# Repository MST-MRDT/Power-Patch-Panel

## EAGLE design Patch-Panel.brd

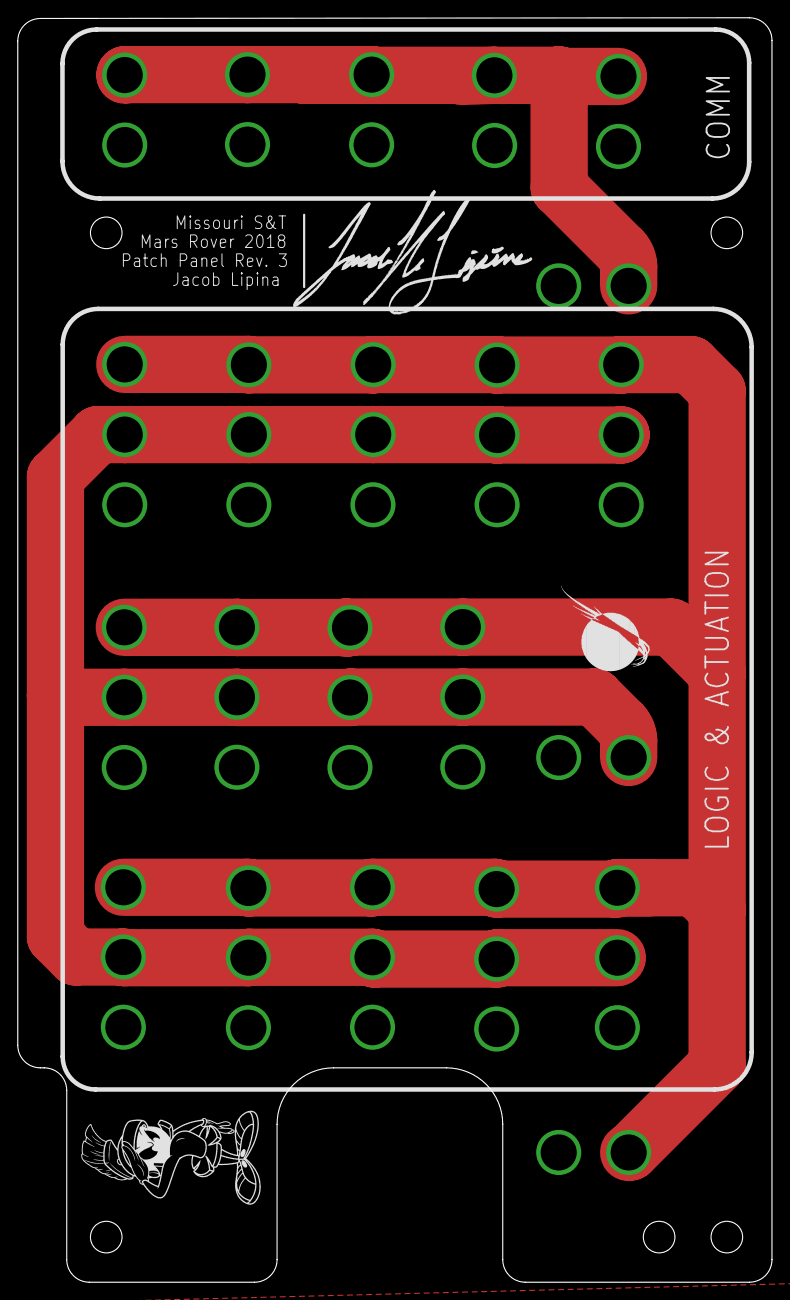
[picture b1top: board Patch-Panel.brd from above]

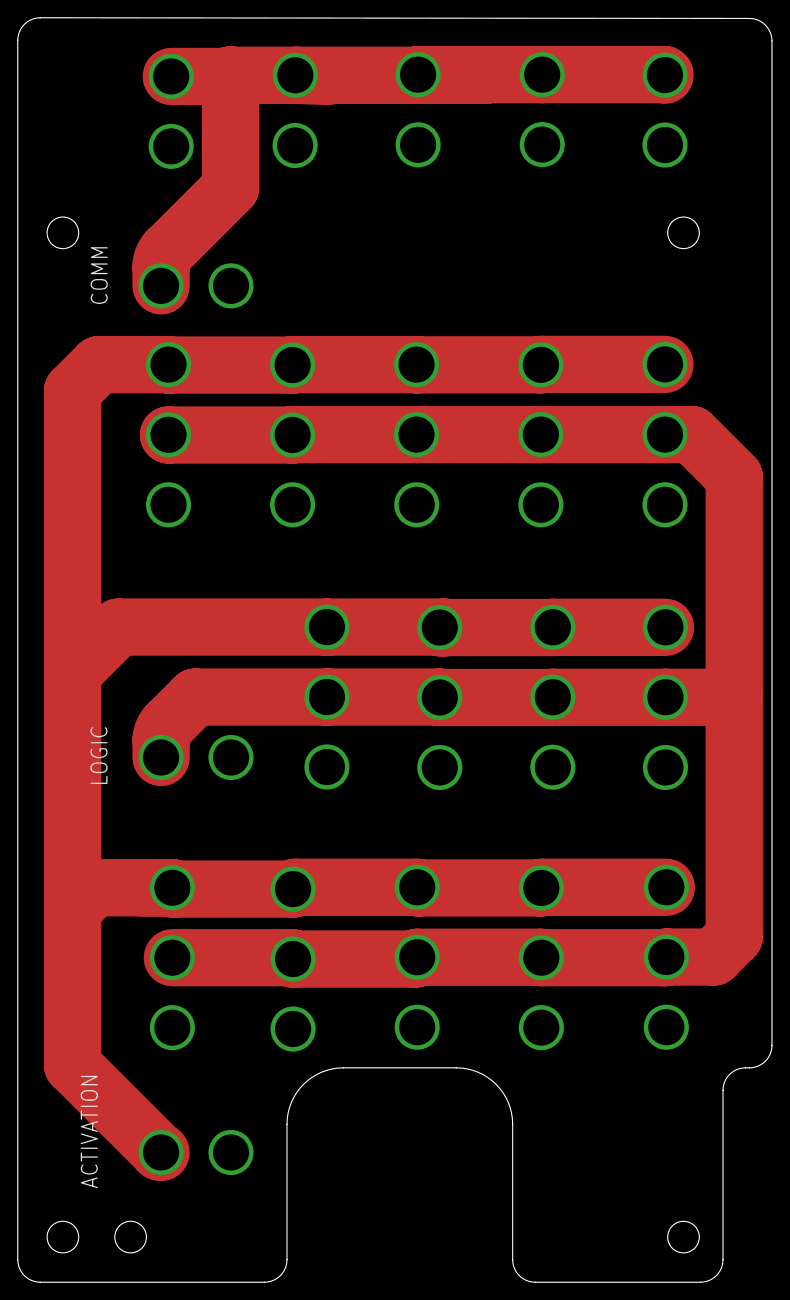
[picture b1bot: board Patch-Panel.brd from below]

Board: 2 copper layers, 84.9 x 142.3 mm, 66 parts (6 on the bottom side), 4 nets.

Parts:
H3, H4, H5, H6, H7: MOUNTING_HOLE#6; #6_SCREW
J1, J2, J3, J4, J5, J6, J7, J8, J9, J10, J11, J12, J13, J14, J15, J16, J17, J18, J19, J20, J21, J22, J23, J24, J25, J26, J27, J28, J29, J30, J31, J32, J33, J34, J35, J36, J37, J38, J39, J40, J41, J42, J43, J44, J45, J46, J47, J48, J49, J50, J51, J52, J53, J54, J55, J56, J57, J58: APPPP45_PCB_VERT; APP45_PCB_VERT
LOGO1: MRDT_LOGO
U$1: JACOB_SIG
U$2: MARVIN-THE-MARTIAN; MARVIN

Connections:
ACT-12V: J1.P$1, J9.P$1, J12.P$1, J15.P$1, J18.P$1, J21.P$1, J24.P$1, J27.P$1, J38.P$1, J41.P$1, J46.P$1, J49.P$1, J52.P$1, J55.P$1, J58.P$1
COM-12V: J5.P$1, J28.P$1, J30.P$1, J32.P$1, J34.P$1, J44.P$1
GND: J2.P$1, J4.P$1, J6.P$1, J7.P$1, J10.P$1, J13.P$1, J16.P$1, J19.P$1, J22.P$1, J25.P$1, J29.P$1, J31.P$1, J33.P$1, J35.P$1, J36.P$1, J39.P$1, J42.P$1, J45.P$1, J47.P$1, J50.P$1, J53.P$1, J56.P$1
LOG-12V: J3.P$1, J8.P$1, J11.P$1, J14.P$1, J17.P$1, J20.P$1, J23.P$1, J26.P$1, J37.P$1, J40.P$1, J43.P$1, J48.P$1, J51.P$1, J54.P$1, J57.P$1

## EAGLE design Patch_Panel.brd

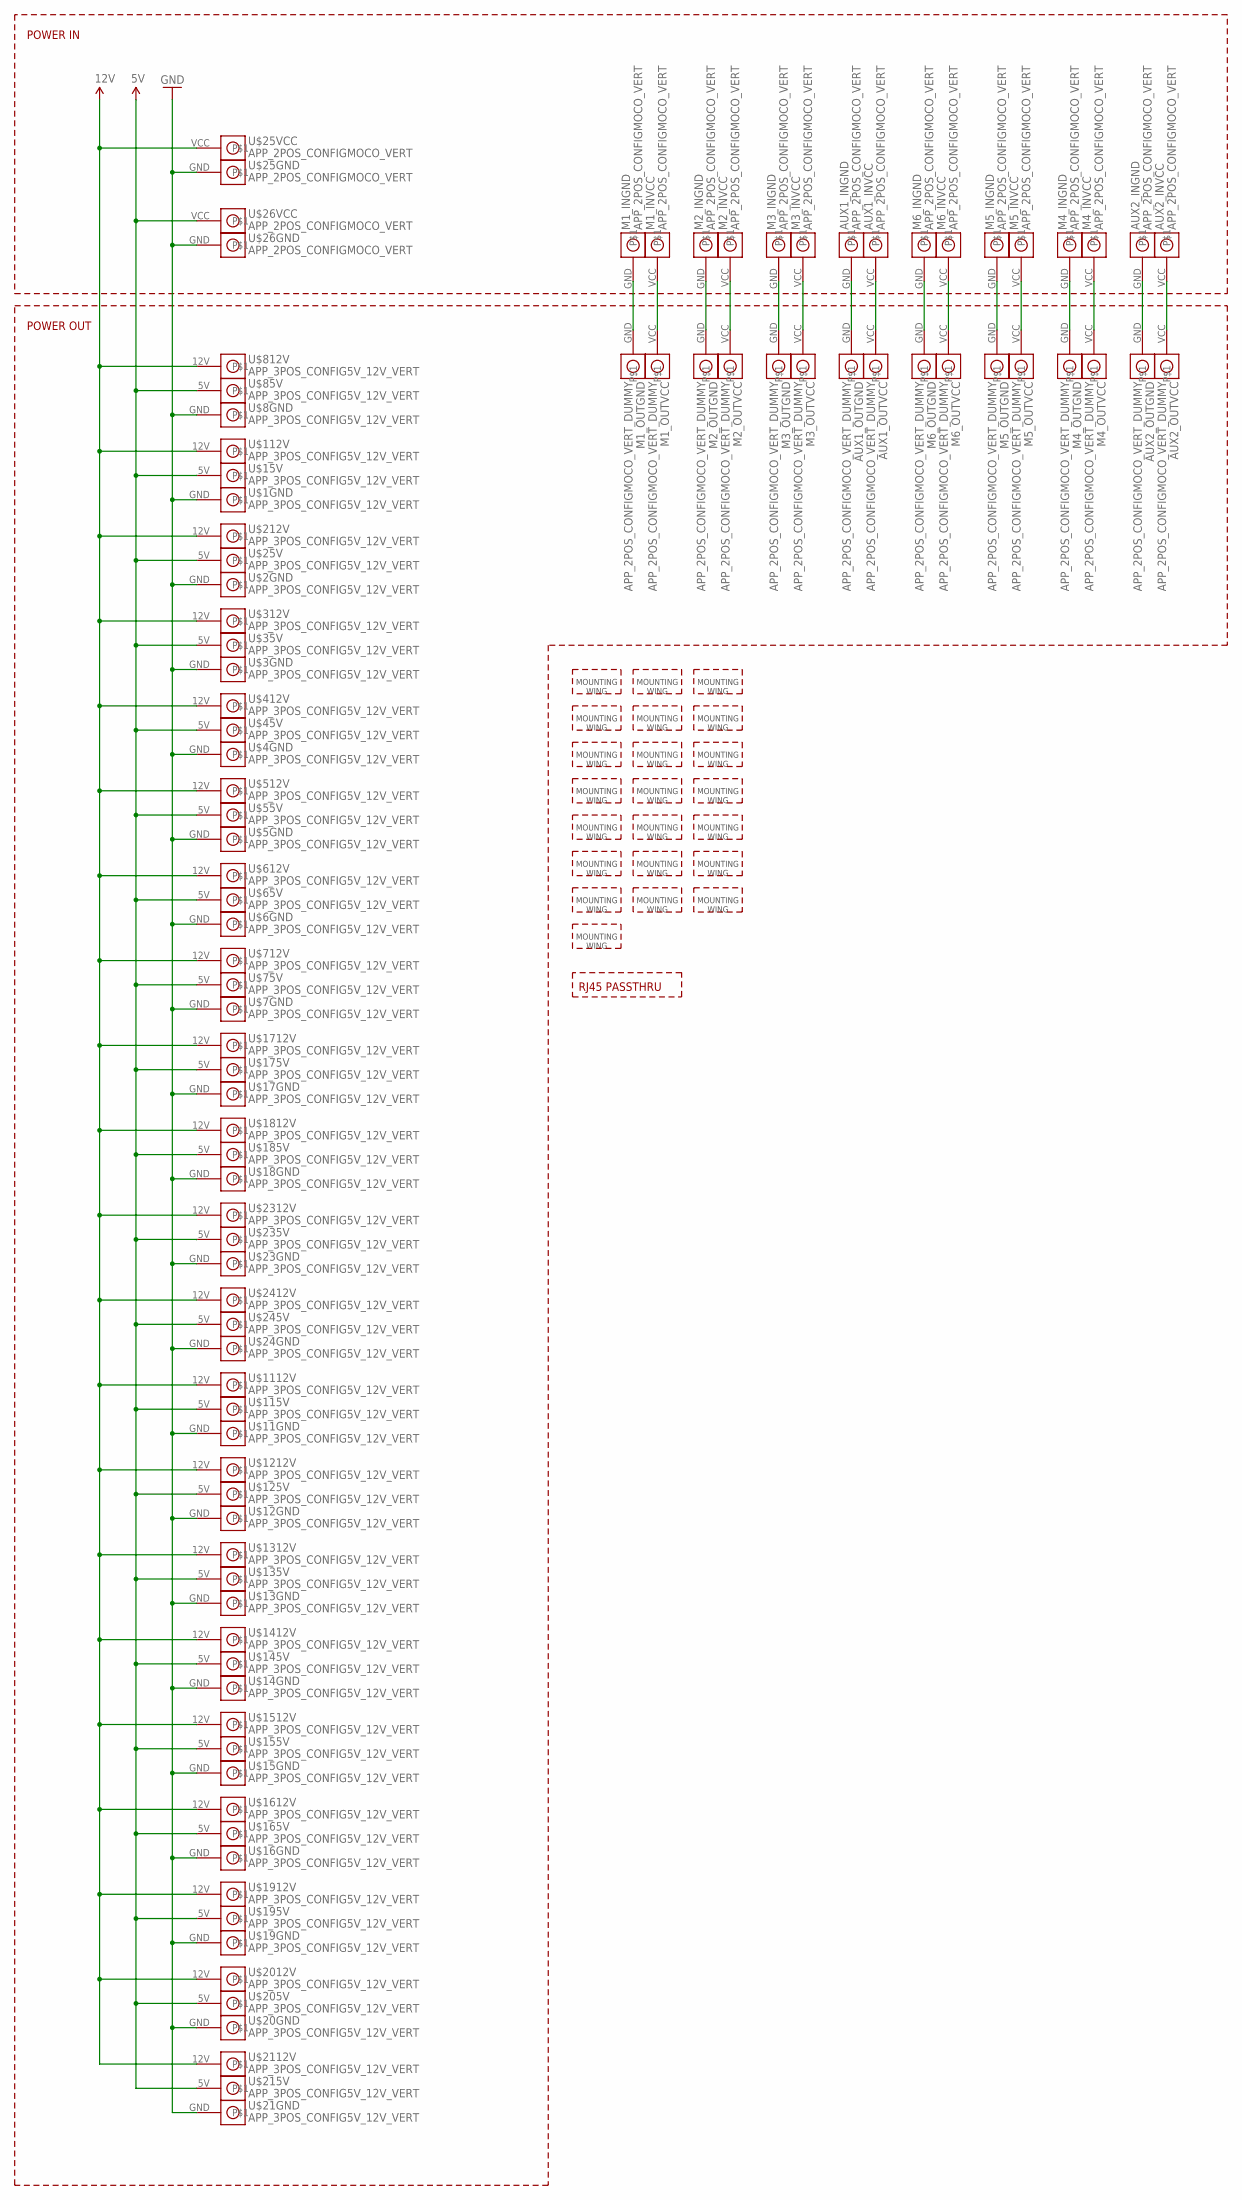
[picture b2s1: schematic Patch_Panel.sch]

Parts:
AUX1_IN, AUX2_IN: APP_2POS_CONFIGMOCO_VERT; APP45_MOCO_VERT_CONFIG
AUX1_OUT, AUX2_OUT: APP_2POS_CONFIGMOCO_VERT_DUMMY; APP45_MOCO_VERT_CONFIG_DUMMY
M1_IN, M2_IN, M3_IN, M4_IN, M5_IN, M6_IN: APP_2POS_CONFIGMOCO_VERT; APP45_MOCO_VERT_CONFIG
M1_OUT, M2_OUT, M3_OUT, M4_OUT, M5_OUT, M6_OUT: APP_2POS_CONFIGMOCO_VERT_DUMMY; APP45_MOCO_VERT_CONFIG_DUMMY
U$1, U$2, U$3, U$4, U$5, U$6, U$7, U$8, U$11, U$12, U$13, U$14, U$15, U$16, U$17, U$18, U$19, U$20, U$21, U$23, U$24: APP_3POS_CONFIG5V_12V_VERT; APP45_5V_12V_VERT_CONFIG
U$9, U$10, U$22, U$27, U$28, U$29, U$30, U$31, U$32, U$33, U$34, U$35, U$36, U$37, U$38, U$39, U$40, U$41, U$42, U$43, U$44, U$45: APP_MOUTING_WINGVERT; APP45_MOUNTING_WING_VERT
U$25, U$26: APP_2POS_CONFIGMOCO_VERT; APP45_MOCO_VERT_CONFIG
U$46: RJ45_PASSTHRUMRDT_MALE_RJ45_STANDOFF; MRDT_MALE_RJ45_STANDOFF

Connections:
5V: U$1.5V, U$2.5V, U$3.5V, U$4.5V, U$5.5V, U$6.5V, U$7.5V, U$8.5V, U$11.5V, U$12.5V, U$13.5V, U$14.5V, U$15.5V, U$16.5V, U$17.5V, U$18.5V, U$19.5V, U$20.5V, U$21.5V, U$23.5V, U$24.5V, U$26.VCC
12V: U$1.12V, U$2.12V, U$3.12V, U$4.12V, U$5.12V, U$6.12V, U$7.12V, U$8.12V, U$11.12V, U$12.12V, U$13.12V, U$14.12V, U$15.12V, U$16.12V, U$17.12V, U$18.12V, U$19.12V, U$20.12V, U$21.12V, U$23.12V, U$24.12V, U$25.VCC
AUX1_VCC: AUX1_IN.VCC, AUX1_OUT.VCC
AUX2_VCC: AUX2_IN.VCC, AUX2_OUT.VCC
GND: AUX1_IN.GND, AUX1_OUT.GND, AUX2_IN.GND, AUX2_OUT.GND, M1_IN.GND, M1_OUT.GND, M2_IN.GND, M2_OUT.GND, M3_IN.GND, M3_OUT.GND, M4_IN.GND, M4_OUT.GND, M5_IN.GND, M5_OUT.GND, M6_IN.GND, M6_OUT.GND, U$1.GND, U$2.GND, U$3.GND, U$4.GND, U$5.GND, U$6.GND, U$7.GND, U$8.GND, U$11.GND, U$12.GND, U$13.GND, U$14.GND, U$15.GND, U$16.GND, U$17.GND, U$18.GND, U$19.GND, U$20.GND, U$21.GND, U$23.GND, U$24.GND, U$25.GND, U$26.GND
M1_VCC: M1_IN.VCC, M1_OUT.VCC
M2_VCC: M2_IN.VCC, M2_OUT.VCC
M3_VCC: M3_IN.VCC, M3_OUT.VCC
M4_VCC: M4_IN.VCC, M4_OUT.VCC
M5_VCC: M5_IN.VCC, M5_OUT.VCC
M6_VCC: M6_IN.VCC, M6_OUT.VCC

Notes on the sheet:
POWER IN
POWER OUT

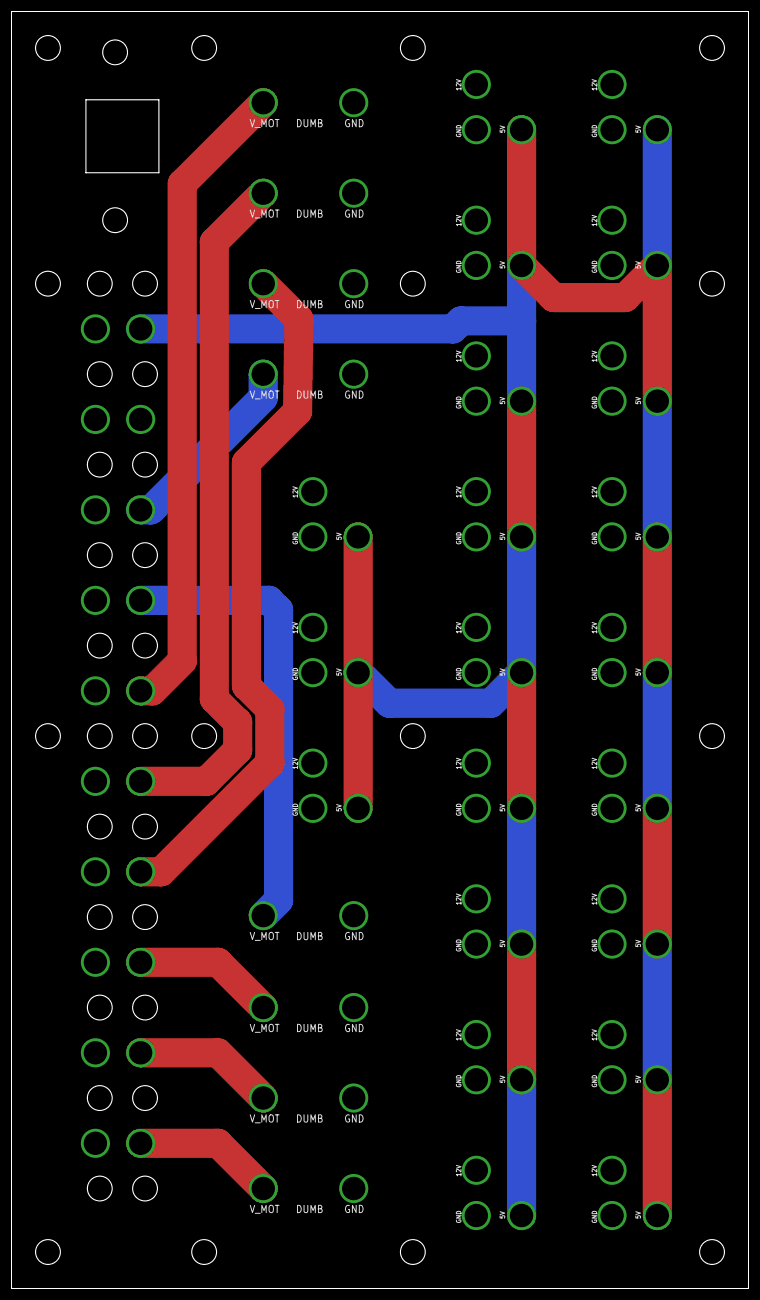
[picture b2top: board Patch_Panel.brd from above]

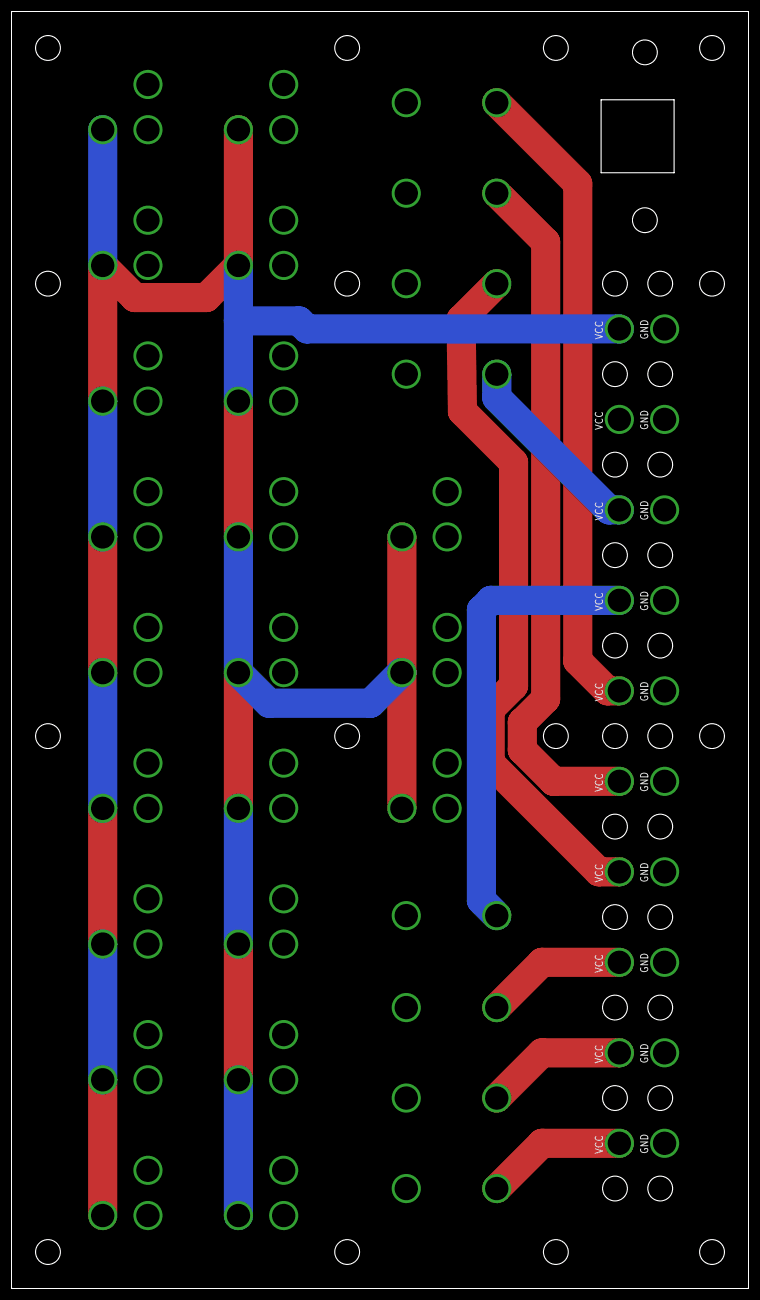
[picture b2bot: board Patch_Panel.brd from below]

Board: 2 copper layers, 128.3 x 222.2 mm, 62 parts (32 on the bottom side), 11 nets.

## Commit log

2015-11-01 Create patch panel V1
2015-11-01 Added BOM
2015-11-17 Remove unnecessary backup files
2015-11-17 Update gitignore
2015-12-02 Removed 2-pin Connectors and RJ45 Pass-Through
2016-01-13 added moco power patch-thru, rearr 3-pin, gen dx
2016-01-13 Revert "added moco power patch-thru, rearr 3-pin, gen dx"
    This reverts commit e393c53abb352ea2a1f007c95e73af8e49a976a5.
2016-01-13 un-deleted brd file and re-added dxf
2016-01-13 imported new mlx connectors
2016-01-15 totally re-made patch panel, gen dxf
2016-01-15 added missing route
2016-01-16 Added ethernet hole
2016-01-19 added cutout, rerouted w/ vert app connectors for power in
2016-01-19 added rj45 standoff - needs placed
2016-01-21 github sucks. i changed some stuff
2016-01-22 FINAL PATCH PANEL REV 1
2016-11-06 2017 Patch Panel
    This patch panel for 2017 has 4 connections for the Logic bus, 6
    connections for the Logic & Actuation bus, 4 connections for the
    Actuation bus, and 2 connections for an extra bus.
2016-11-08 Last edits before fabrication
    tidied a couple traces and labels, and added a martian.
2017-11-08 2018 Patch Panel Rev1
    The 12V buses are being passed to patch panel. In order from bottom of power board to top, Actuation 15A, Logic 5A, Communication 5A. There is no extra bus this year. Add one more Logic/Act connection
2017-11-09 Font changed to vector
2018-03-15 Patch Panel Rev 2
    Eliminates all exclusive logic buses and added seven more actuation/logic combo buses. Added one more comm bus
2018-03-25 Rev.3 to Change Mounting Hole Locations
    Mounting holes on Rev.2 are incorrect because power board's size changed slightly and we only realized the holes didnt match up after we ordered Rev.2
2018-03-26 Adjusted bottom anderson positions
2018-03-26 Added gitignore and fixed silkscreen
2018-12-07 Created project and completed schematic
2018-12-13 Added Packages to Library
2018-12-13 Symbols named and packages assigned
2018-12-13 Outline and Hole Placement Complete
2018-12-13 Placed Double Andersons
2018-12-14 Placed Connectors & Routed Traces
2018-12-14 Added Silkscreen
2018-12-14 Created BOM
2018-12-31 Created Gerbs
2019-01-17 update rev 2 library
2019-10-08 layout
2019-10-10 board
2019-10-10 finished PCBdesign
2019-10-10 ready for PDR
2019-10-31 ready for board review
2019-11-18 add input label
2019-11-21 final change
2019-11-21 before review
2019-11-26 fixed board review issue
2019-12-06 matching
2019-12-11 change molex
2019-12-11 add LED to anderson
2019-12-11 BoardReview
2019-12-11 add gerbs
2019-12-14 bom.scv
2019-12-15 fix bom file
2020-01-21 Created Step File
2020-03-06 Redid entire schematic to be more organized and compact
2020-03-06 added some silks, generated Gerbs

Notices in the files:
parts and their libraries:
SparkFun-Aesthetics: Licensing: Creative Commons ShareAlike 4.0 International - https://creativecommons.org/licenses/by-sa/4.0
